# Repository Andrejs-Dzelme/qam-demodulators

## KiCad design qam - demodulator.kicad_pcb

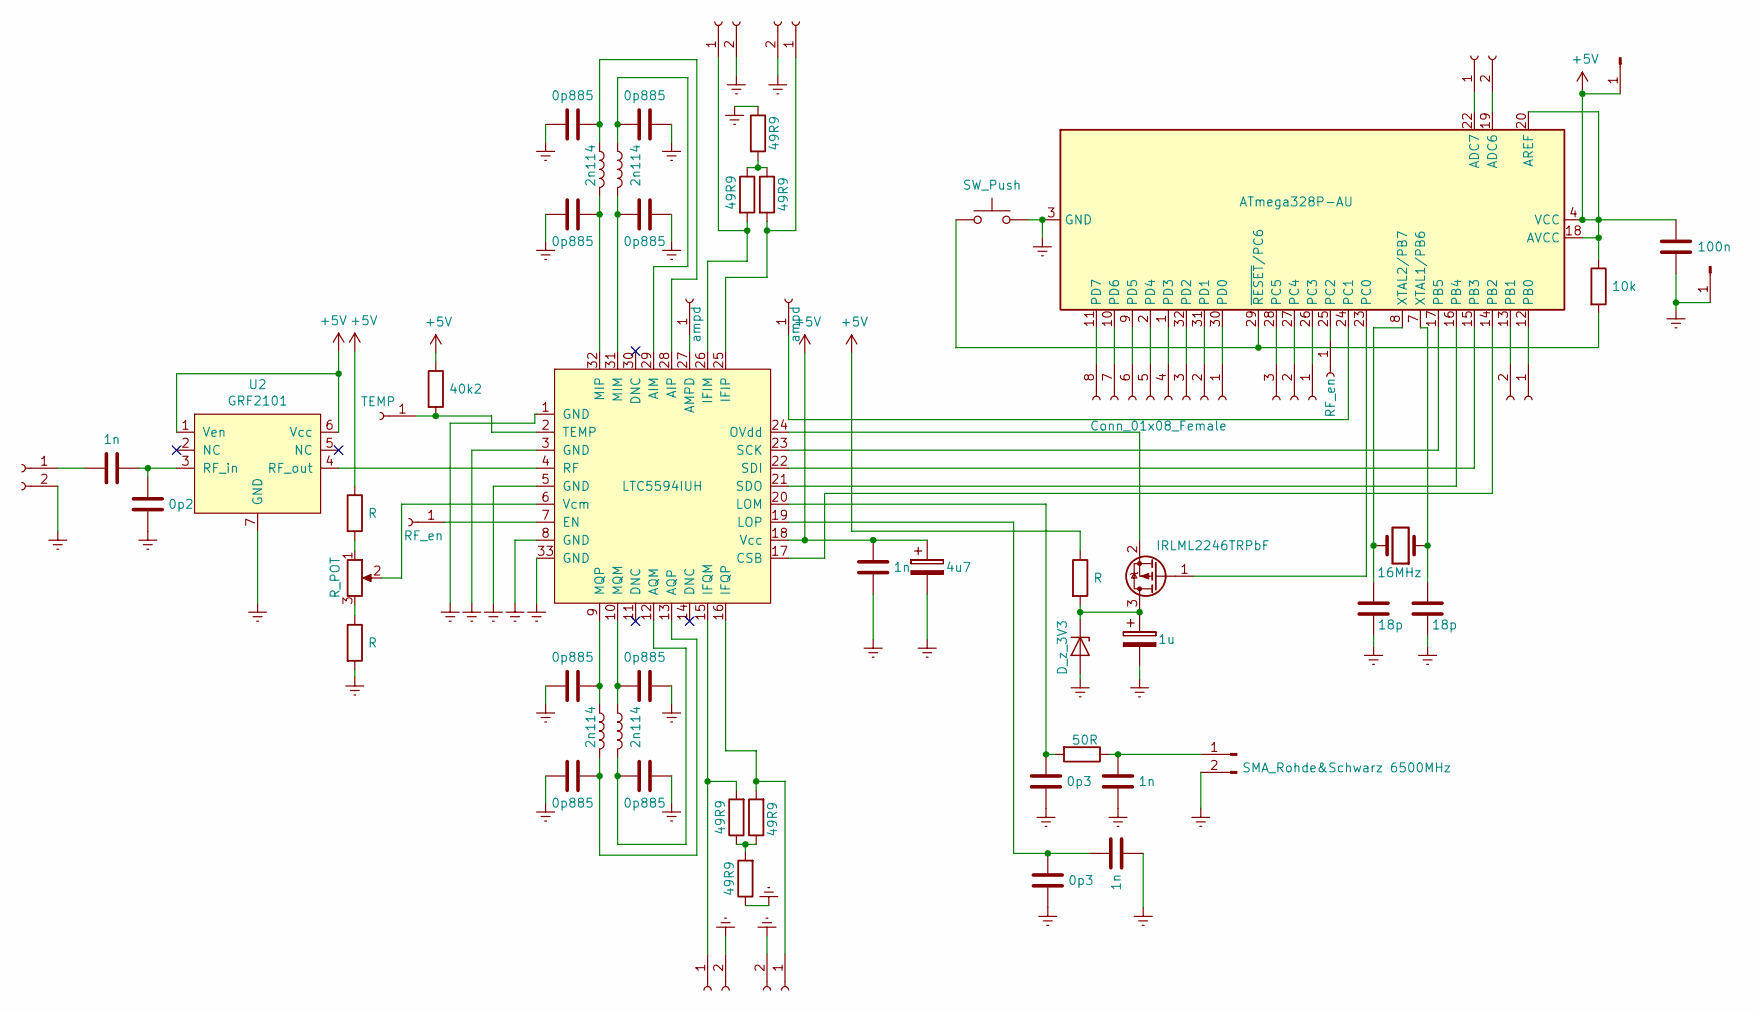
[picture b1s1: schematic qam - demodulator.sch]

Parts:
C1, C17, C18, C19: 1n; C_0201_0603Metric
C2: 4u7; CP_Radial_Tantal_D8.0mm_P5.00mm
C3: 1u; C_1210_3225Metric
C4, C5: 18p; C_0201_0603Metric
C6: 100n; C_0201_0603Metric
C7, C8, C9, C10, C11, C12, C13, C14: 0p885; C_0201_0603Metric
C15, C16: 0p3; C_0201_0603Metric
C20: 0p2; C_0201_0603Metric
D1: D_z_3V3; C_Axial_L3.8mm_D2.6mm_P10.00mm_Horizontal
J1: TEMP; PinHeader_1x01_P1.00mm_Vertical
J2: SMA_Rohde&Schwarz 6500MHz; SMA_Amphenol_132289_EdgeMount
J3: Conn_01x08_Female; PinHeader_1x08_P1.00mm_Vertical
J4: Conn_01x03_Female; PinHeader_1x03_P1.00mm_Vertical
J5, J6: Conn_01x02_Female; PinHeader_1x02_P1.00mm_Vertical
J7, J8: Conn_01x01_Male; PinHeader_1x01_P2.54mm_Vertical
J9, J10, J11, J12, J13: Connector_Conn_01x02_Female; SMA_Amphenol_132289_EdgeMount
J14, J15: RF_en; PinHeader_1x01_P1.00mm_Vertical
J16, J17: ampd; PinHeader_1x01_P1.00mm_Vertical
L1, L2, L3, L4: 2n114; C_0201_0603Metric
Q1: IRLML2246TRPbF; SOT-23
R1, R2: R; C_0805_2012Metric_Pad1.15x1.40mm_HandSolder
R3: 40k2; C_0805_2012Metric_Pad1.15x1.40mm_HandSolder
R4: R; C_0201_0603Metric
R5: 10k; C_0805_2012Metric_Pad1.15x1.40mm_HandSolder
R6: 50R; C_0201_0603Metric
RV1: R_POT; Potentiometer_ACP_CA6-H2,5_Horizontal
SW1: SW_Push; PinHeader_1x03_P2.54mm_Vertical
U2: GRF2101; DFN-6-1EP_2x2mm_P0.65mm_EP1x1.6mm
U5: LTC5594IUH; LFCSP-32-1EP_5x5mm_P0.5mm_EP3.25x3.25mm
U8: ATmega328P-AU; TQFP-32_7x7mm_P0.8mm
Y1: 16MHz; C_Axial_L3.8mm_D2.6mm_P7.50mm_Horizontal
r1, r2, r3, r4, r5, r6: 49R9; C_0201_0603Metric

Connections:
+5V: C1.1, C2.1, C6.1, J7.1, R1.1, R3.1, R4.1, R5.1, U2.1 (Ven), U2.6 (Vcc), U5.18 (Vcc), U8.4 (VCC), U8.6 (VCC), U8.18 (AVCC), U8.20 (AREF); also elsewhere on the board
GNDREF: C1.2, C2.2, C3.2, C4.2, C5.2, C6.2, C7.2, C8.2, C9.2, C10.2, C11.1, C12.1, C13.1, C14.1, C15.2, C16.2, C17.1, C18.2, C20.2, D1.2 (A), J2.2, J8.1, J9.2, J10.2, J11.2, J12.2, J13.2, R2.2, SW1.2, U2.7 (GND), U5.1 (GND), U5.3 (GND), U5.5 (GND), U5.8 (GND), U5.33 (GND), U8.3 (GND), U8.5 (GND), U8.21 (GND), r2.1, r5.1
unnamed: C3.1, D1.1 (K), Q1.3 (D), R4.2
unnamed: C4.1, U8.8 (XTAL2/PB7), Y1.2
unnamed: C5.1, U8.7 (XTAL1/PB6), Y1.1
unnamed: C7.1, L1.1, U5.28 (AIP)
unnamed: C8.1, L1.2, U5.32 (MIP)
unnamed: C9.1, L2.1, U5.9 (MQP)
unnamed: C10.1, L2.2, U5.13 (AQP)
unnamed: C11.2, L3.1, U5.29 (AIM)
unnamed: C12.2, L3.2, U5.31 (MIM)
unnamed: C13.2, L4.1, U5.10 (MQM)
unnamed: C14.2, L4.2, U5.12 (AQM)
unnamed: C15.1, R6.2, U5.20 (LOM)
unnamed: C16.1, C17.2, U5.19 (LOP)
unnamed: C18.1, J2.1, R6.1
unnamed: C19.1, C20.1, U2.3 (RF_in)
unnamed: C19.2, J9.1
unnamed: J1.1, R3.2, U5.2 (TEMP)
unnamed: J3.1, U8.30 (PD0)
unnamed: J3.2, U8.31 (PD1)
unnamed: J3.3, U8.32 (PD2)
unnamed: J3.4, U8.1 (PD3)
unnamed: J3.5, U8.2 (PD4)
unnamed: J3.6, U8.9 (PD5)
unnamed: J3.7, U8.10 (PD6)
unnamed: J3.8, U8.11 (PD7)
unnamed: J4.1, U8.26 (PC3)
unnamed: J4.2, U8.27 (PC4)
unnamed: J4.3, U8.28 (PC5)
unnamed: J5.1, U8.22 (ADC7)
unnamed: J5.2, U8.19 (ADC6)
unnamed: J6.1, U8.12 (PB0)
unnamed: J6.2, U8.13 (PB1)
unnamed: J10.1, U5.26 (IFIM), r3.2
unnamed: J11.1, U5.15 (IFQM), r1.2
unnamed: J12.1, U5.25 (IFIP), r6.2
unnamed: J13.1, U5.16 (IFQP), r4.2
unnamed: J14.1, U5.7 (EN)
unnamed: J15.1, U8.25 (PC2)
unnamed 40: J16.1, U5.27 (AMPD); also elsewhere on the board
unnamed 41: J17.1, U8.24 (PC1); also elsewhere on the board
unnamed: Q1.1 (G), U8.23 (PC0)
unnamed: Q1.2 (S), U5.24 (OVdd)
unnamed: R1.2, RV1.1
unnamed: R2.1, RV1.3
unnamed: R5.2, SW1.1, U8.29 (~RESET~/PC6)
unnamed: RV1.2, U5.6 (Vcm)
unnamed: U2.4 (RF_out), U5.4 (RF)
unnamed: U5.17 (CSB), U8.14 (PB2)
unnamed: U5.21 (SDO), U8.16 (PB4)
unnamed: U5.22 (SDI), U8.15 (PB3)
unnamed: U5.23 (SCK), U8.17 (PB5)
unnamed: r1.1, r2.2, r4.1
unnamed: r3.1, r5.2, r6.1

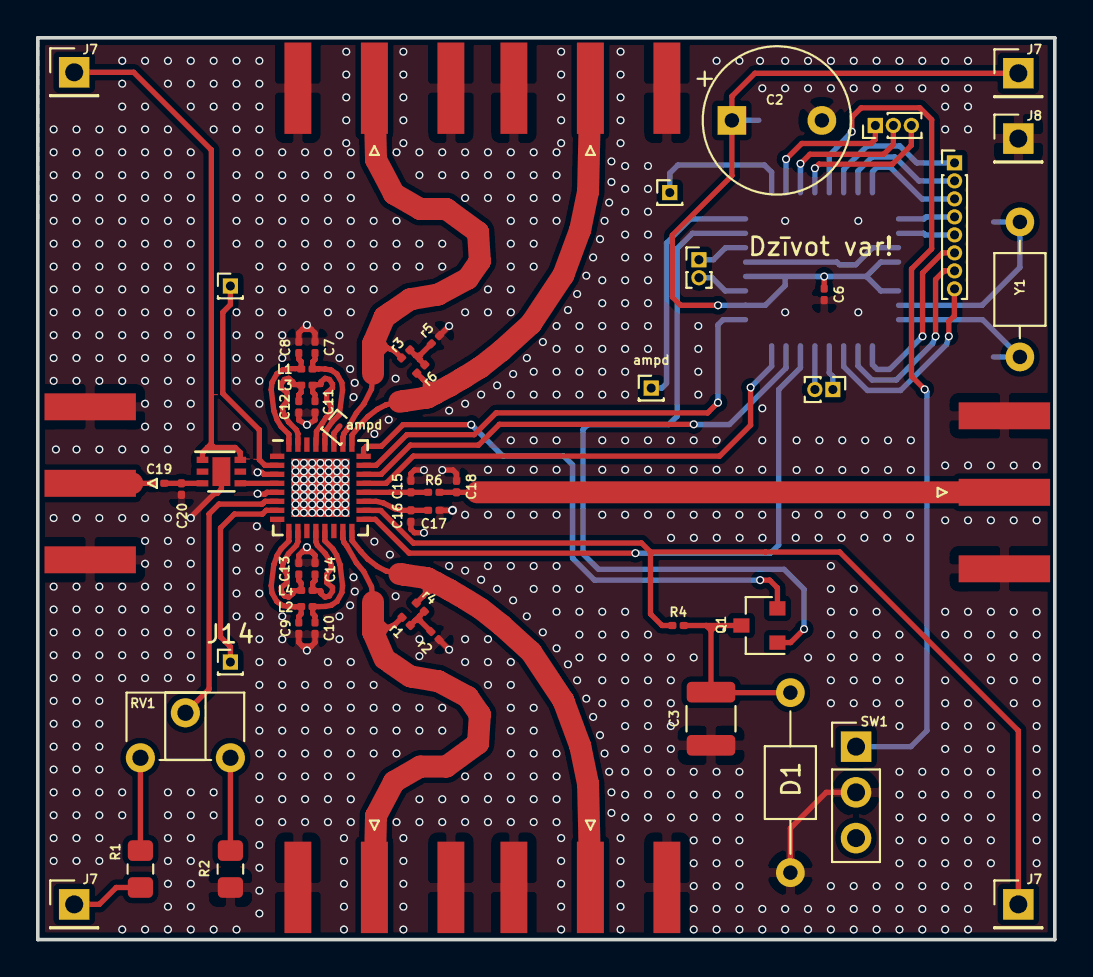
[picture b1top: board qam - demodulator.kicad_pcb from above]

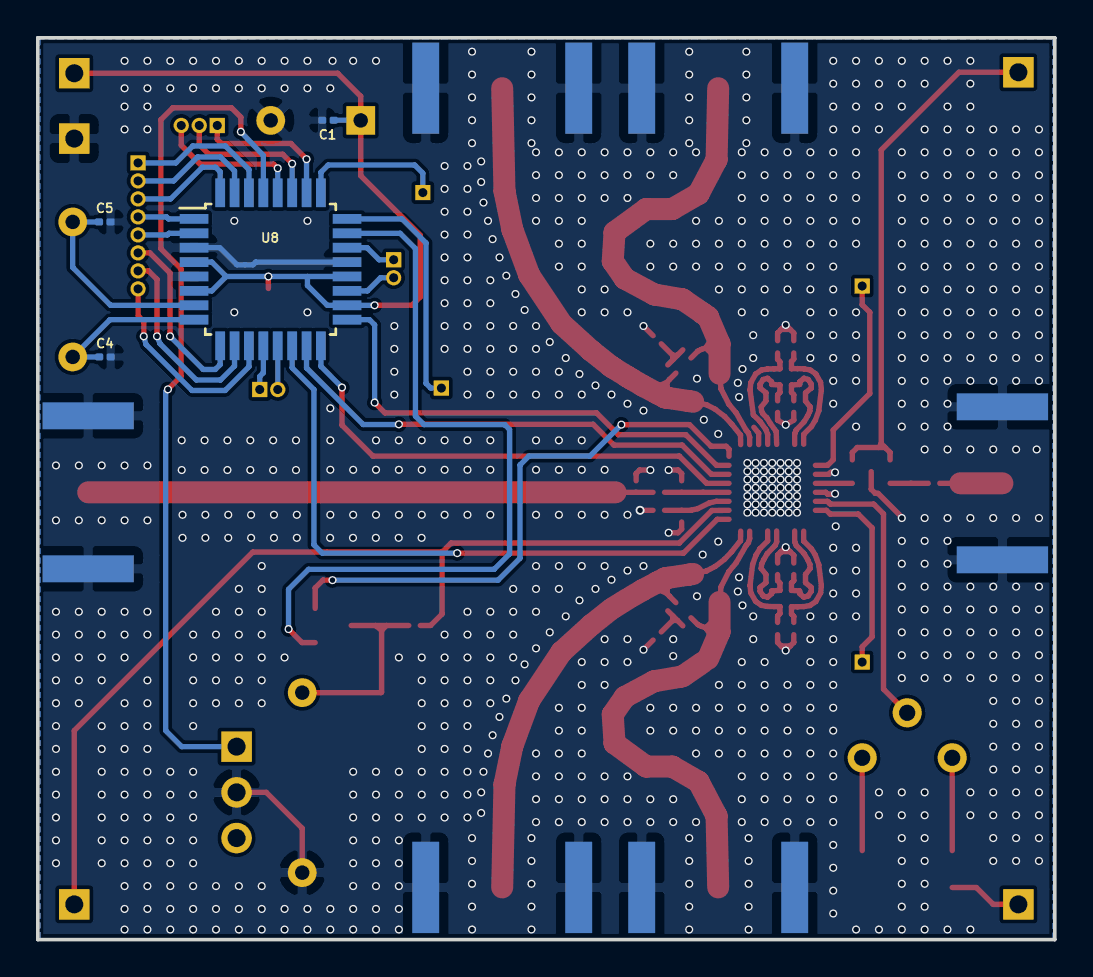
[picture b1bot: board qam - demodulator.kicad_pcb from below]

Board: 2 copper layers, 56.5 x 50.1 mm, 62 parts (4 on the bottom side), 55 nets.

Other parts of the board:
J7#2, J7#3, J7#4: Conn_01x01_Male; PinHeader_1x01_P2.54mm_Vertical
ampd: ampd; PinHeader_1x01_P1.00mm_Vertical
ampd#2: ampd; PinHeader_1x01_P1.00mm_Vertical

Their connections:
+5V: J7#2.1, J7#3.1, J7#4.1; also elsewhere on the board
unnamed 40: ampd.1; also elsewhere on the board
unnamed 41: ampd#2.1; also elsewhere on the board
